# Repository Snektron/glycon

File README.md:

nin# Glycon

## Dependencies

* meson
* ninja or samurai
* avr-binutils
* avr-gcc
* avr-libc

## Compiling

### Coprocessor

```
$ mkdir -p build/glyco
$ cd build/glyco
$ meson ../.. --cross-file ../../cross/avr-atmega2560-cross.ini
$ ninja
```

To use the provided `flash` target to flash the coprocessor, set the coprocessor port the arduino is connected with by passing `-Dport=/dev/<port>` to meson (usually /dev/ttyUSB0) and add yourself to to appropriate groups (typically `dialout` or `uucp`).

### Debugger

```
$ mkdir -p build/glydb
$ cd build/glydb
$ meson ../..
$ ninja
```

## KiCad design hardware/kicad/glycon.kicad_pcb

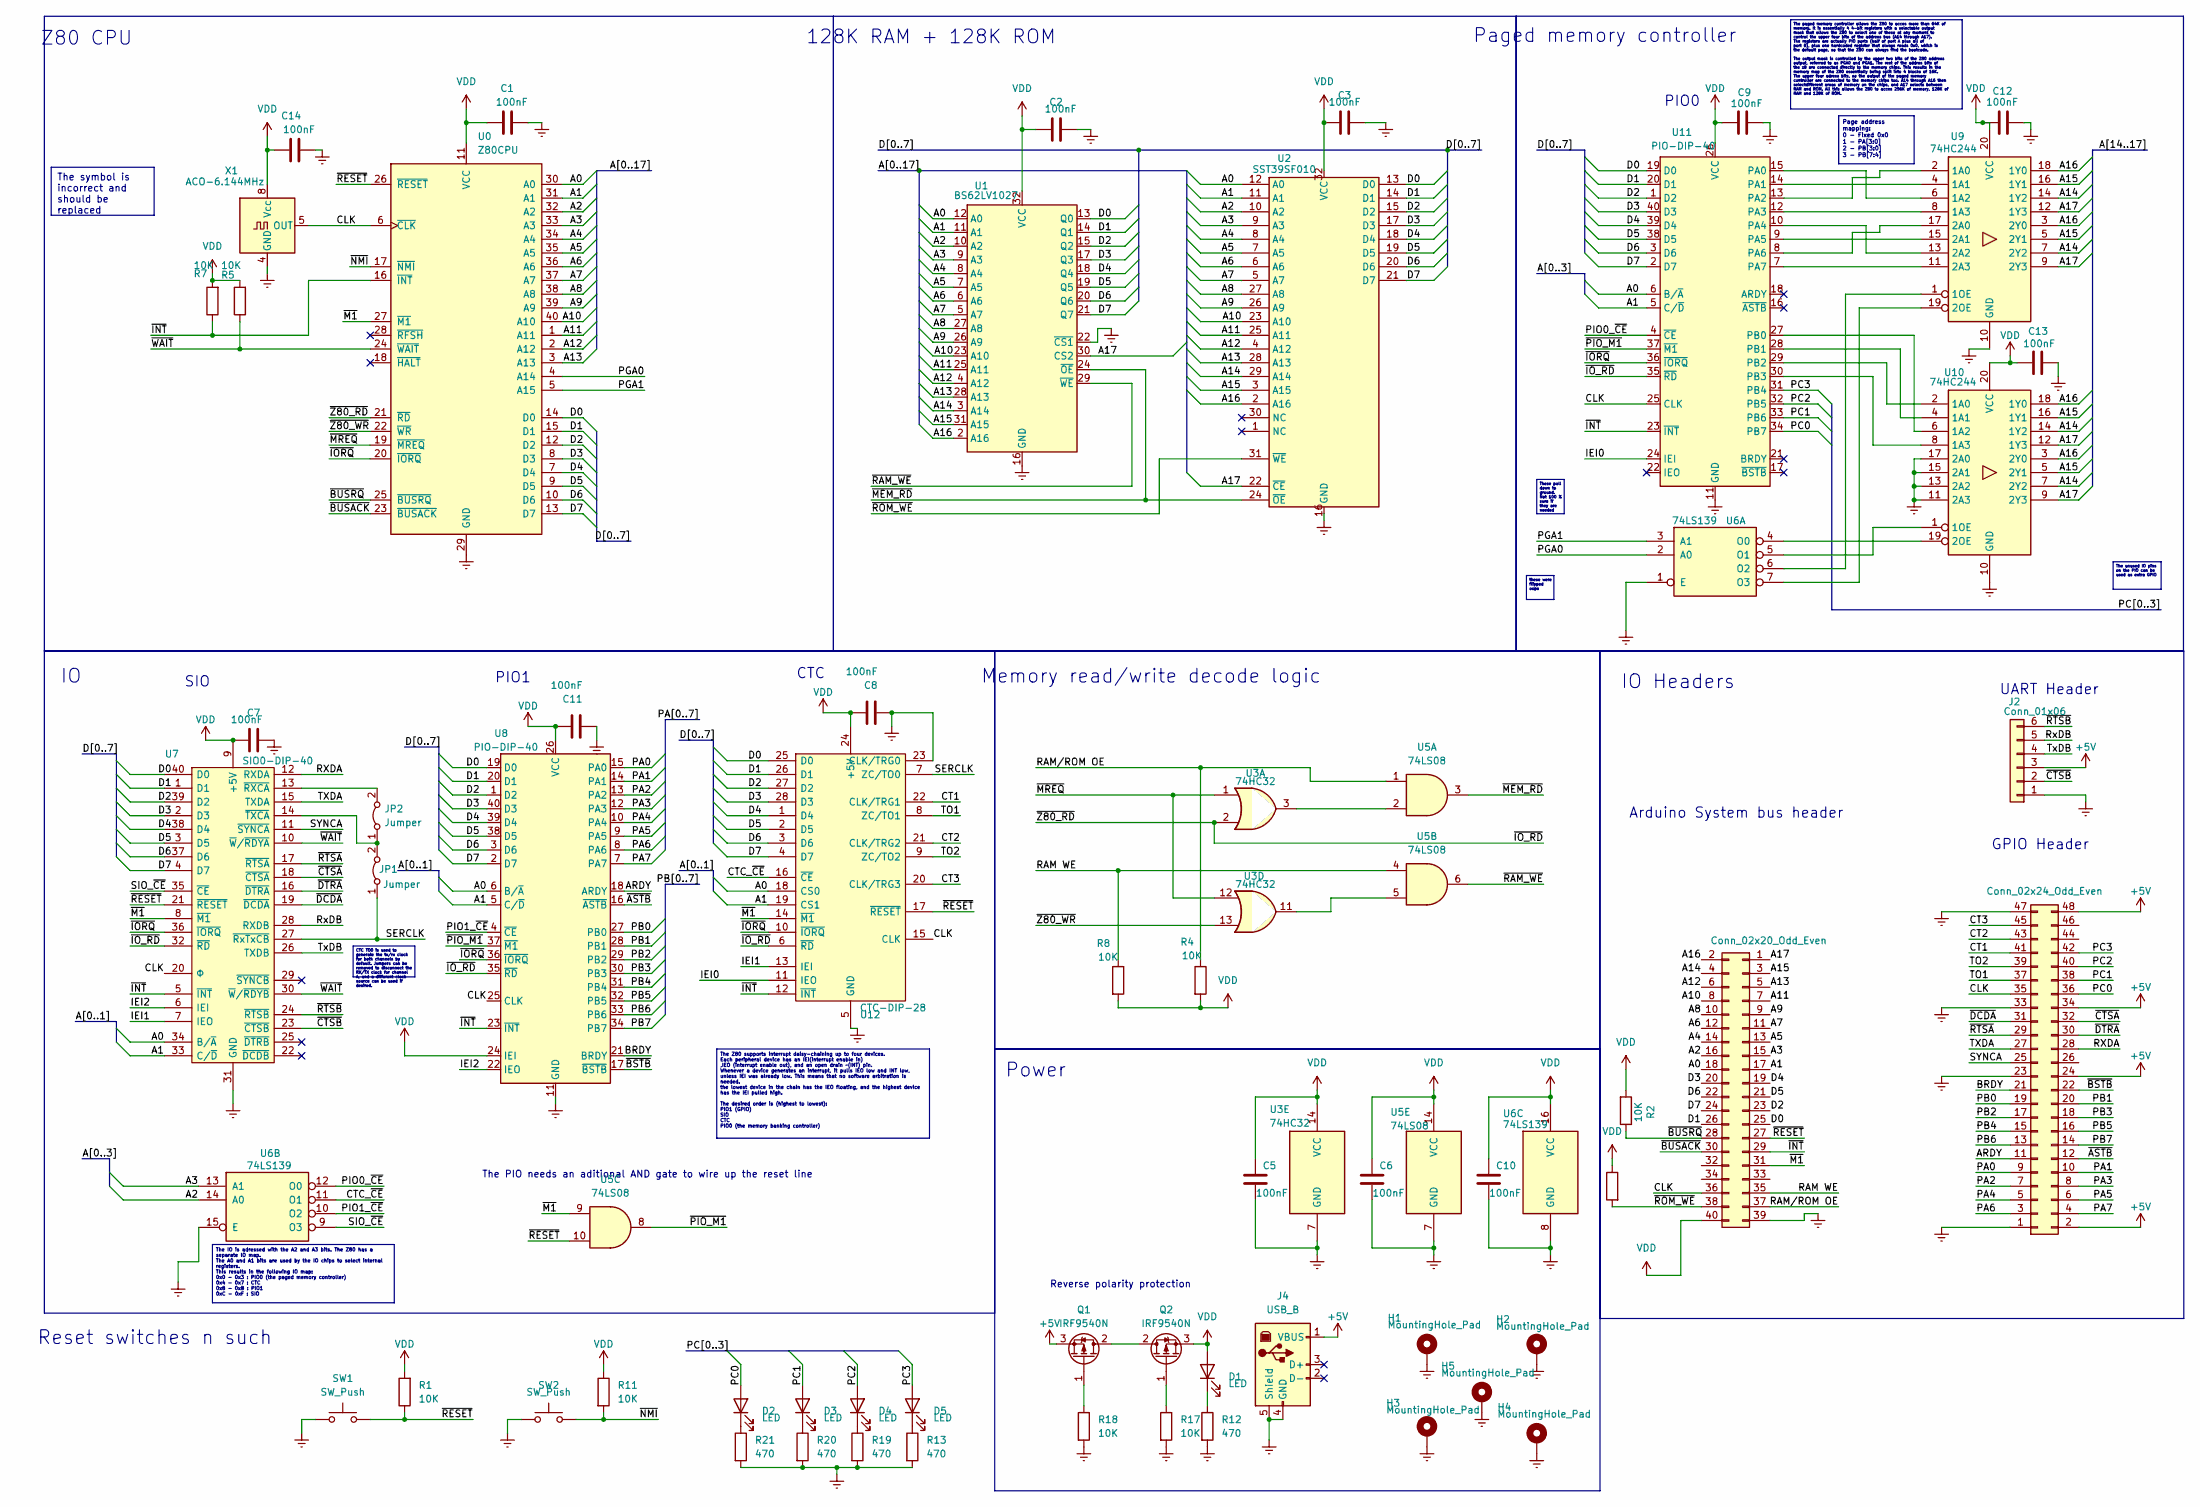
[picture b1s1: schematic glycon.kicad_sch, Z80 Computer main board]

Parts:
C1, C2, C3, C5, C6, C7, C8, C9, C10, C11, C12, C13, C14: 100nF; C_Disc_D4.7mm_W2.5mm_P5.00mm
D1, D2, D3, D4, D5: LED; LED_D5.0mm
H1, H2, H3, H4, H5: MountingHole_Pad; MountingHole_3.2mm_M3_Pad
J1: Conn_02x20_Odd_Even; PinSocket_2x20_P2.54mm_Vertical
J2: Conn_01x06; PinHeader_1x06_P2.54mm_Vertical
J3: Conn_02x24_Odd_Even; PinSocket_2x24_P2.54mm_Vertical
J4: USB_B; USB_B_TE_5787834_Vertical
JP1, JP2: Jumper; PinHeader_2x01_P2.54mm_Vertical
Q1, Q2: IRF9540N; TO-220-3_Vertical
R1, R2, R3, R4, R5, R7, R8, R11, R17, R18: 10K; R_Axial_DIN0207_L6.3mm_D2.5mm_P10.16mm_Horizontal
R12, R13, R19, R20, R21: 470; R_Axial_DIN0207_L6.3mm_D2.5mm_P10.16mm_Horizontal
SW1, SW2: SW_Push; SW_PUSH_6mm
U0: Z80CPU; DIP-40_W15.24mm_Socket
U1: BS62LV1027; DIP-32_W15.24mm_Socket
U2: SST39SF010; DIP-32_W15.24mm_Socket
U3: 74HC32; DIP-14_W7.62mm_Socket
U5: 74LS08; DIP-14_W7.62mm_Socket
U6: 74LS139; DIP-16_W7.62mm_Socket
U7: SIO0-DIP-40; DIP-40_W15.24mm_Socket; Manufacturer_Part_Number Z84C4206PEG; Mouser Part Number 692-Z84C4206PEG
U8, U11: PIO-DIP-40; DIP-40_W15.24mm_Socket
U9, U10: 74HC244; DIP-20_W7.62mm_Socket
U12: CTC-DIP-28; DIP-28_W15.24mm_Socket; Manufacturer_Part_Number Z84C3010PEG; Mouser Part Number 692-Z84C3010PEG
X1: ACO-6.144MHz; Oscillator_DIP-8

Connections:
+5V: J2.3, J3.2, J3.24, J3.34, J3.48, J4.1 (VBUS), Q1.3 (S)
/A0: J1.18, U0.30 (A0), U1.12 (A0), U2.12 (A0), U7.34 (B/~A), U8.6 (B/~A), U11.6 (B/~A), U12.18 (CS0)
/A1: J1.17, U0.31 (A1), U1.11 (A1), U2.11 (A1), U7.33 (C/~D), U8.5 (C/~D), U11.5 (C/~D), U12.19 (CS1)
/A2: J1.16, U0.32 (A2), U1.10 (A2), U2.10 (A2), U6.14 (A0)
/A3: J1.15, U0.33 (A3), U1.9 (A3), U2.9 (A3), U6.13 (A1)
/A4: J1.14, U0.34 (A4), U1.8 (A4), U2.8 (A4)
/A5: J1.13, U0.35 (A5), U1.7 (A5), U2.7 (A5)
/A6: J1.12, U0.36 (A6), U1.6 (A6), U2.6 (A6)
/A7: J1.11, U0.37 (A7), U1.5 (A7), U2.5 (A7)
/A8: J1.10, U0.38 (A8), U1.27 (A8), U2.27 (A8)
/A9: J1.9, U0.39 (A9), U1.26 (A9), U2.26 (A9)
/A10: J1.8, U0.40 (A10), U1.23 (A10), U2.23 (A10)
/A11: J1.7, U0.1 (A11), U1.25 (A11), U2.25 (A11)
/A12: J1.6, U0.2 (A12), U1.4 (A12), U2.4 (A12)
/A13: J1.5, U0.3 (A13), U1.28 (A13), U2.28 (A13)
/A14: J1.4, U1.3 (A14), U2.29 (A14), U9.7 (2Y2), U9.14 (1Y2), U10.7 (2Y2), U10.14 (1Y2)
/A15: J1.3, U1.31 (A15), U2.3 (A15), U9.5 (2Y1), U9.16 (1Y1), U10.5 (2Y1), U10.16 (1Y1)
/A16: J1.2, U1.2 (A16), U2.2 (A16), U9.3 (2Y0), U9.18 (1Y0), U10.3 (2Y0), U10.18 (1Y0)
/A17: J1.1, U1.30 (CS2), U2.22 (~CE), U9.9 (2Y3), U9.12 (1Y3), U10.9 (2Y3), U10.12 (1Y3)
/ARDY: J3.11, U8.18 (ARDY)
/BRDY: J3.21, U8.21 (BRDY)
/CLK: J1.36, J3.35, U0.6 (~CLK), U7.20 (Φ), U8.25 (CLK), U11.25 (CLK), U12.15 (CLK), X1.5 (OUT)
/CT1: J3.41, U12.22 (CLK/TRG1)
/CT2: J3.43, U12.21 (CLK/TRG2)
/CT3: J3.45, U12.20 (CLK/TRG3)
/CTC_~CE: U6.11 (O1), U12.16 (~CE)
/D0: J1.25, U0.14 (D0), U1.13 (Q0), U2.13 (D0), U7.40 (D0), U8.19 (D0), U11.19 (D0), U12.25 (D0)
/D1: J1.26, U0.15 (D1), U1.14 (Q1), U2.14 (D1), U7.1 (D1), U8.20 (D1), U11.20 (D1), U12.26 (D1)
/D2: J1.23, U0.12 (D2), U1.15 (Q2), U2.15 (D2), U7.39 (D2), U8.1 (D2), U11.1 (D2), U12.27 (D2)
/D3: J1.20, U0.8 (D3), U1.17 (Q3), U2.17 (D3), U7.2 (D3), U8.40 (D3), U11.40 (D3), U12.28 (D3)
/D4: J1.19, U0.7 (D4), U1.18 (Q4), U2.18 (D4), U7.38 (D4), U8.39 (D4), U11.39 (D4), U12.1 (D4)
/D5: J1.21, U0.9 (D5), U1.19 (Q5), U2.19 (D5), U7.3 (D5), U8.38 (D5), U11.38 (D5), U12.2 (D5)
/D6: J1.22, U0.10 (D6), U1.20 (Q6), U2.20 (D6), U7.37 (D6), U8.3 (D6), U11.3 (D6), U12.3 (D6)
/D7: J1.24, U0.13 (D7), U1.21 (Q7), U2.21 (D7), U7.4 (D7), U8.2 (D7), U11.2 (D7), U12.4 (D7)
/IEI0: U11.24 (IEI), U12.11 (IEO)
/IEI1: U7.7 (IEO), U12.13 (IEI)
/IEI2: U7.6 (IEI), U8.22 (IEO)
/PA0: J3.9, U8.15 (PA0)
/PA1: J3.10, U8.14 (PA1)
/PA2: J3.7, U8.13 (PA2)
/PA3: J3.8, U8.12 (PA3)
/PA4: J3.5, U8.10 (PA4)
/PA5: J3.6, U8.9 (PA5)
/PA6: J3.3, U8.8 (PA6)
/PA7: J3.4, U8.7 (PA7)
/PB0: J3.19, U8.27 (PB0)
/PB1: J3.20, U8.28 (PB1)
/PB2: J3.17, U8.29 (PB2)
/PB3: J3.18, U8.30 (PB3)
/PB4: J3.15, U8.31 (PB4)
/PB5: J3.16, U8.32 (PB5)
/PB6: J3.13, U8.33 (PB6)
/PB7: J3.14, U8.34 (PB7)
/PC0: D2.2 (A), J3.36, U11.34 (PB7)
/PC1: D3.2 (A), J3.38, U11.33 (PB6)
/PC2: D4.2 (A), J3.40, U11.32 (PB5)
/PC3: D5.2 (A), J3.42, U11.31 (PB4)
/PGA0: U0.4 (A14), U6.2 (A0)
/PGA1: U0.5 (A15), U6.3 (A1)
/PIO0_~CE: U6.12 (O0), U11.4 (~CE)
/PIO1_~CE: U6.10 (O2), U8.4 (~CE)
/RAM WE: J1.35, R8.1, U5.4
/RAM/ROM OE: J1.37, R4.1, U5.1
/RXDA: J3.28, U7.12 (RXDA)
/RxDB: J2.5, U7.28 (RXDB)
/SERCLK: JP1.1 (A), U7.27 (~RxTxCB), U12.7 (ZC/TO0)
/SIO_~CE: U6.9 (O3), U7.35 (~CE)
/SYNCA: J3.25, U7.11 (~SYNCA)
/TO1: J3.37, U12.8 (ZC/TO1)
/TO2: J3.39, U12.9 (ZC/TO2)
/TXDA: J3.27, U7.15 (TXDA)
/TxDB: J2.4, U7.26 (TXDB)
/~ASTB: J3.12, U8.16 (~ASTB)
/~BSTB: J3.22, U8.17 (~BSTB)
/~BUSACK: J1.30, U0.23 (~BUSACK)
/~BUSRQ: J1.28, R2.1, U0.25 (~BUSRQ)
/~CTSA: J3.32, U7.18 (~CTSA)
/~CTSB: J2.2, U7.23 (~CTSB)
/~DCDA: J3.31, U7.19 (~DCDA)
/~DTRA: J3.30, U7.16 (~DTRA)
/~INT: J1.29, R7.1, U0.16 (~INT), U7.5 (~INT), U8.23 (~INT), U11.23 (~INT), U12.12 (~INT)
/~IORQ: U0.20 (~IORQ), U7.36 (~IORQ), U8.36 (~IORQ), U11.36 (~IORQ), U12.10 (~IORQ)
/~IO_RD: U0.21 (~RD), U3.2, U7.32 (~RD), U8.35 (~RD), U11.35 (~RD), U12.6 (~RD)
/~M1: J1.31, U0.27 (~M1), U5.9, U7.8 (~M1), U12.14 (~M1)
/~MEM_RD: U1.24 (~OE), U2.24 (~OE), U5.3
/~MREQ: U0.19 (~MREQ), U3.1, U3.12
/~NMI: R11.2, SW2.2, U0.17 (~NMI)
/~PIO_M1: U5.8, U8.37 (~M1), U11.37 (~M1)
/~RAM_WE: U1.29 (~WE), U5.6
/~RESET: J1.27, R1.1, SW1.2, U0.26 (~RESET), U5.10, U7.21 (~RESET), U12.17 (~RESET)
/~ROM_WE: J1.38, R3.2, U2.31 (~WE)
/~RTSA: J3.29, U7.17 (~RTSA)
/~RTSB: J2.6, U7.24 (~RTSB)
/~WAIT: R5.1, U0.24 (~WAIT), U7.10 (~W/~RDYA), U7.30 (~W/~RDYB)
/~Z80_WR: U0.22 (~WR), U3.13
Earth: C1.2, C2.2, C3.1, C5.2, C6.2, C7.2, C8.2, C9.1, C10.2, C11.2, C12.2, C13.2, C14.2, H1.1, H2.1, H3.1, H4.1, H5.1, J1.39, J2.1, J3.1, J3.23, J3.33, J3.47, J4.4 (GND), J4.5 (Shield), R12.2, R13.2, R17.2, R18.2, R19.2, R20.2, R21.2, SW1.1, SW2.1, U0.29 (GND), U1.16 (GND), U1.22 (~CS1), U2.16 (GND), U3.7 (GND), U5.7 (GND), U6.1 (E), U6.8 (GND), U6.15 (E), U7.31 (GND), U8.11 (GND), U9.10 (GND), U10.10 (GND), U10.11 (2A3), U10.13 (2A2), U10.15 (2A1), U10.17 (2A0), U11.11 (GND), U12.5 (GND), U12.23 (CLK/TRG0), X1.4 (GND)
unnamed: D1.1 (K), R12.1
unnamed: D2.1 (K), R21.1
unnamed: D3.1 (K), R20.1
unnamed: D4.1 (K), R19.1
unnamed: D5.1 (K), R13.1
unnamed: JP1.2 (B), JP2.1 (A), U7.14 (~TXCA)
unnamed: JP2.2 (B), U7.13 (~RXCA)
unnamed: Q1.2 (D), Q2.2 (D)
unnamed: Q1.1 (G), R18.1
unnamed: Q2.1 (G), R17.1
unnamed: U3.3, U5.2
unnamed: U3.11, U5.5
unnamed: U6.6 (O2), U9.1 (1OE)
unnamed: U6.7 (O3), U9.19 (2OE)
unnamed: U10.2 (1A0), U11.29 (PB2)
unnamed: U10.4 (1A1), U11.28 (PB1)
unnamed: U10.6 (1A2), U11.27 (PB0)
unnamed: U10.8 (1A3), U11.30 (PB3)
unnamed: U6.5 (O1), U10.1 (1OE)
unnamed: U6.4 (O0), U10.19 (2OE)
unnamed: U9.6 (1A2), U11.15 (PA0)
unnamed: U9.4 (1A1), U11.14 (PA1)
unnamed: U9.2 (1A0), U11.13 (PA2)
unnamed: U9.8 (1A3), U11.12 (PA3)
unnamed: U9.13 (2A2), U11.10 (PA4)
unnamed: U9.15 (2A1), U11.9 (PA5)
unnamed: U9.17 (2A0), U11.8 (PA6)
unnamed: U9.11 (2A3), U11.7 (PA7)
VDD: C1.1, C2.1, C3.2, C5.1, C6.1, C7.1, C8.1, C9.2, C10.1, C11.1, C12.1, C13.1, C14.1, D1.2 (A), J1.40, Q2.3 (S), R1.2, R2.2, R3.1, R4.2, R5.2, R7.2, R8.2, R11.1, U0.11 (VCC), U1.32 (VCC), U2.32 (VCC), U3.14 (VCC), U5.14 (VCC), U6.16 (VCC), U7.9 (+5V), U8.24 (IEI), U8.26 (VCC), U9.20 (VCC), U10.20 (VCC), U11.26 (VCC), U12.24 (+5V), X1.8 (Vcc)

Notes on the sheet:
CTC TO0 is used to generate the tx/rx clock for both channels by default. Jumpers can be removed to disconnect the RX/TX clock for channel A, and a different clock source can be used if desired.
The unused IO pins on the PIO can be used as extra GPIO
The IO is adressed with the A2 and A3 bits. The Z80 has a separate IO map. The A0 and A1 bits are used by the IO chips to select internal registers. This results in the following IO map: 0x0 - 0x3 : PIO0 (the paged memory controller) 0x4 - 0x7 : CTC 0x8 - 0xB : PIO1 0xC - 0xF : SIO
these were flipped oops
These pull down to ground. Not 100 % sure if they are needed
The Z80 supports interrupt daisy-chaining up to four devices. Each peripheral device has an IEI(interrupt enable in) ,IEO (interrupt enable out), and an open drain ~(INT) pin. Whenever a device generates an interrupt, it pulls IEO low and INT low, unless IEI was already low. This means that no soft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
The paged memory controller allows the Z80 to acces more than 64K of memory. It is essentially 4 4-bit registers with a selectable output mask that allows the Z80 to select one of these at any moment to control the upper four bits of the address bus (A14 through A17). The registers are actually PIO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
Page address mapping: 0 - Fixed 0x0 1 - PA[3:0] 2 - PB[3:0] 3 - PB[7:4]
The symbol is incorrect and should be replaced
Reset switches n such
UART Header
CTC
Power
PIO0
Z80 CPU
SIO
IO Headers
128K RAM + 128K ROM
The PIO needs an aditional AND gate to wire up the reset line
Paged memory controller
Reverse polarity protection
GPIO Header
Memory read/write decode logic
Arduino System bus header
PIO1

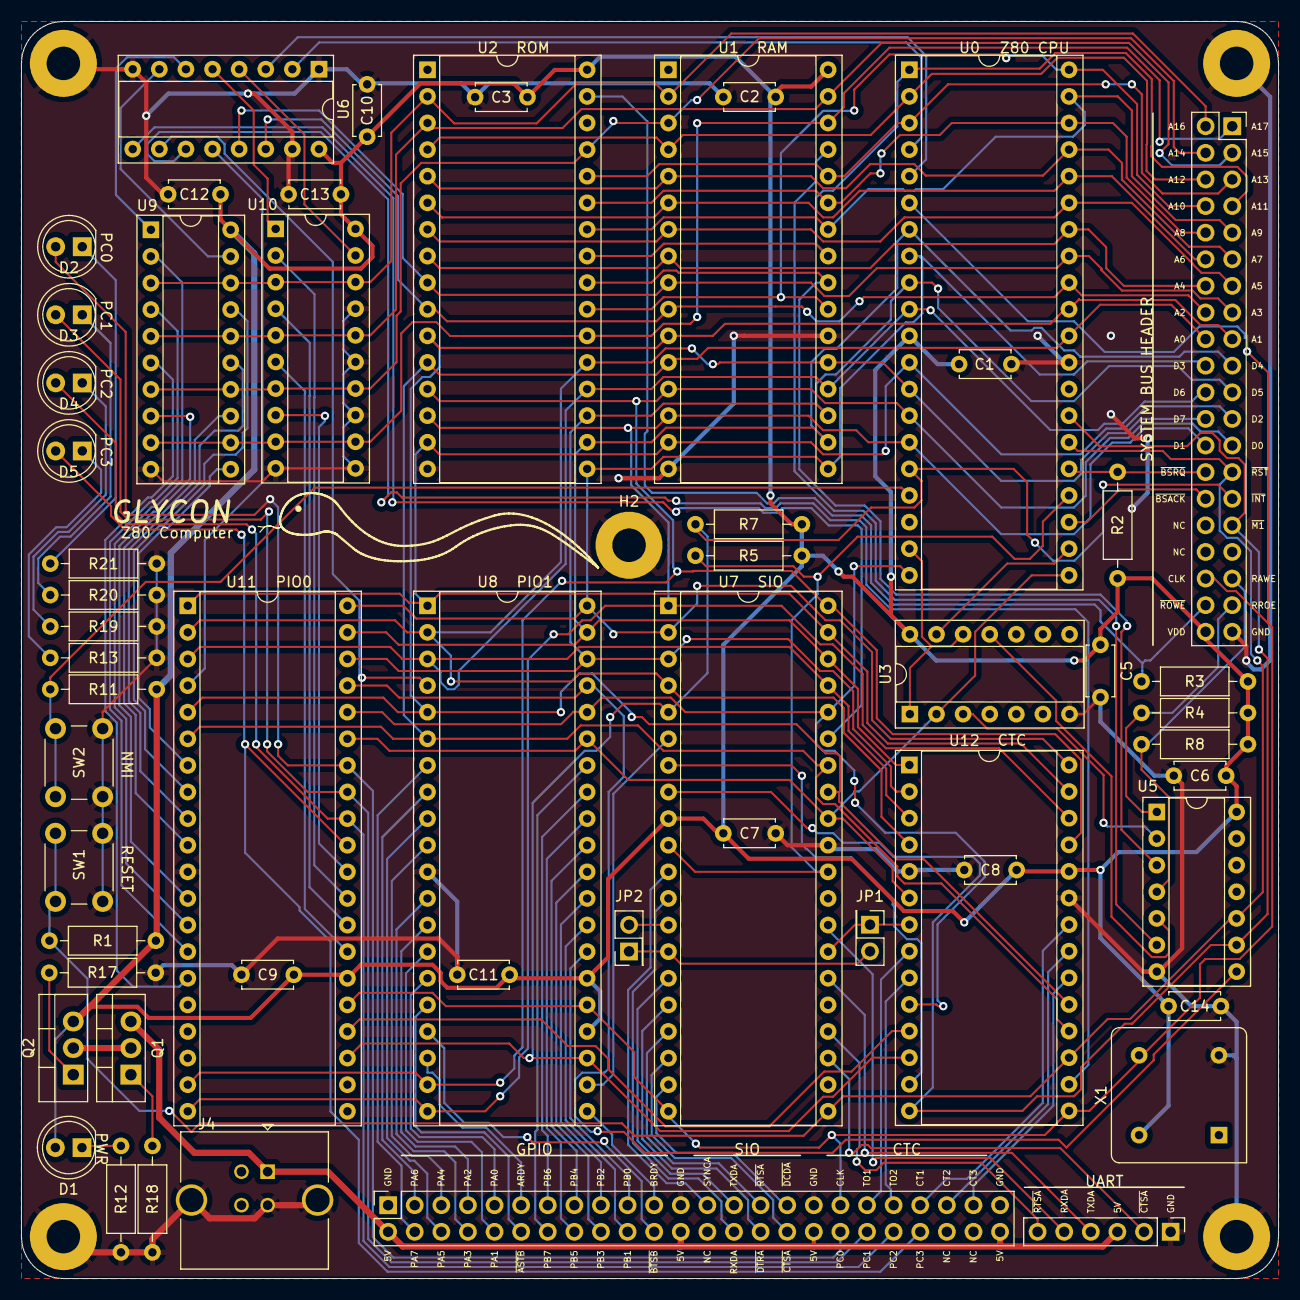
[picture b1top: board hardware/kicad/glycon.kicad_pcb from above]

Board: 2 copper layers, 120.0 x 120.0 mm, 61 parts (0 on the bottom side), 125 nets.

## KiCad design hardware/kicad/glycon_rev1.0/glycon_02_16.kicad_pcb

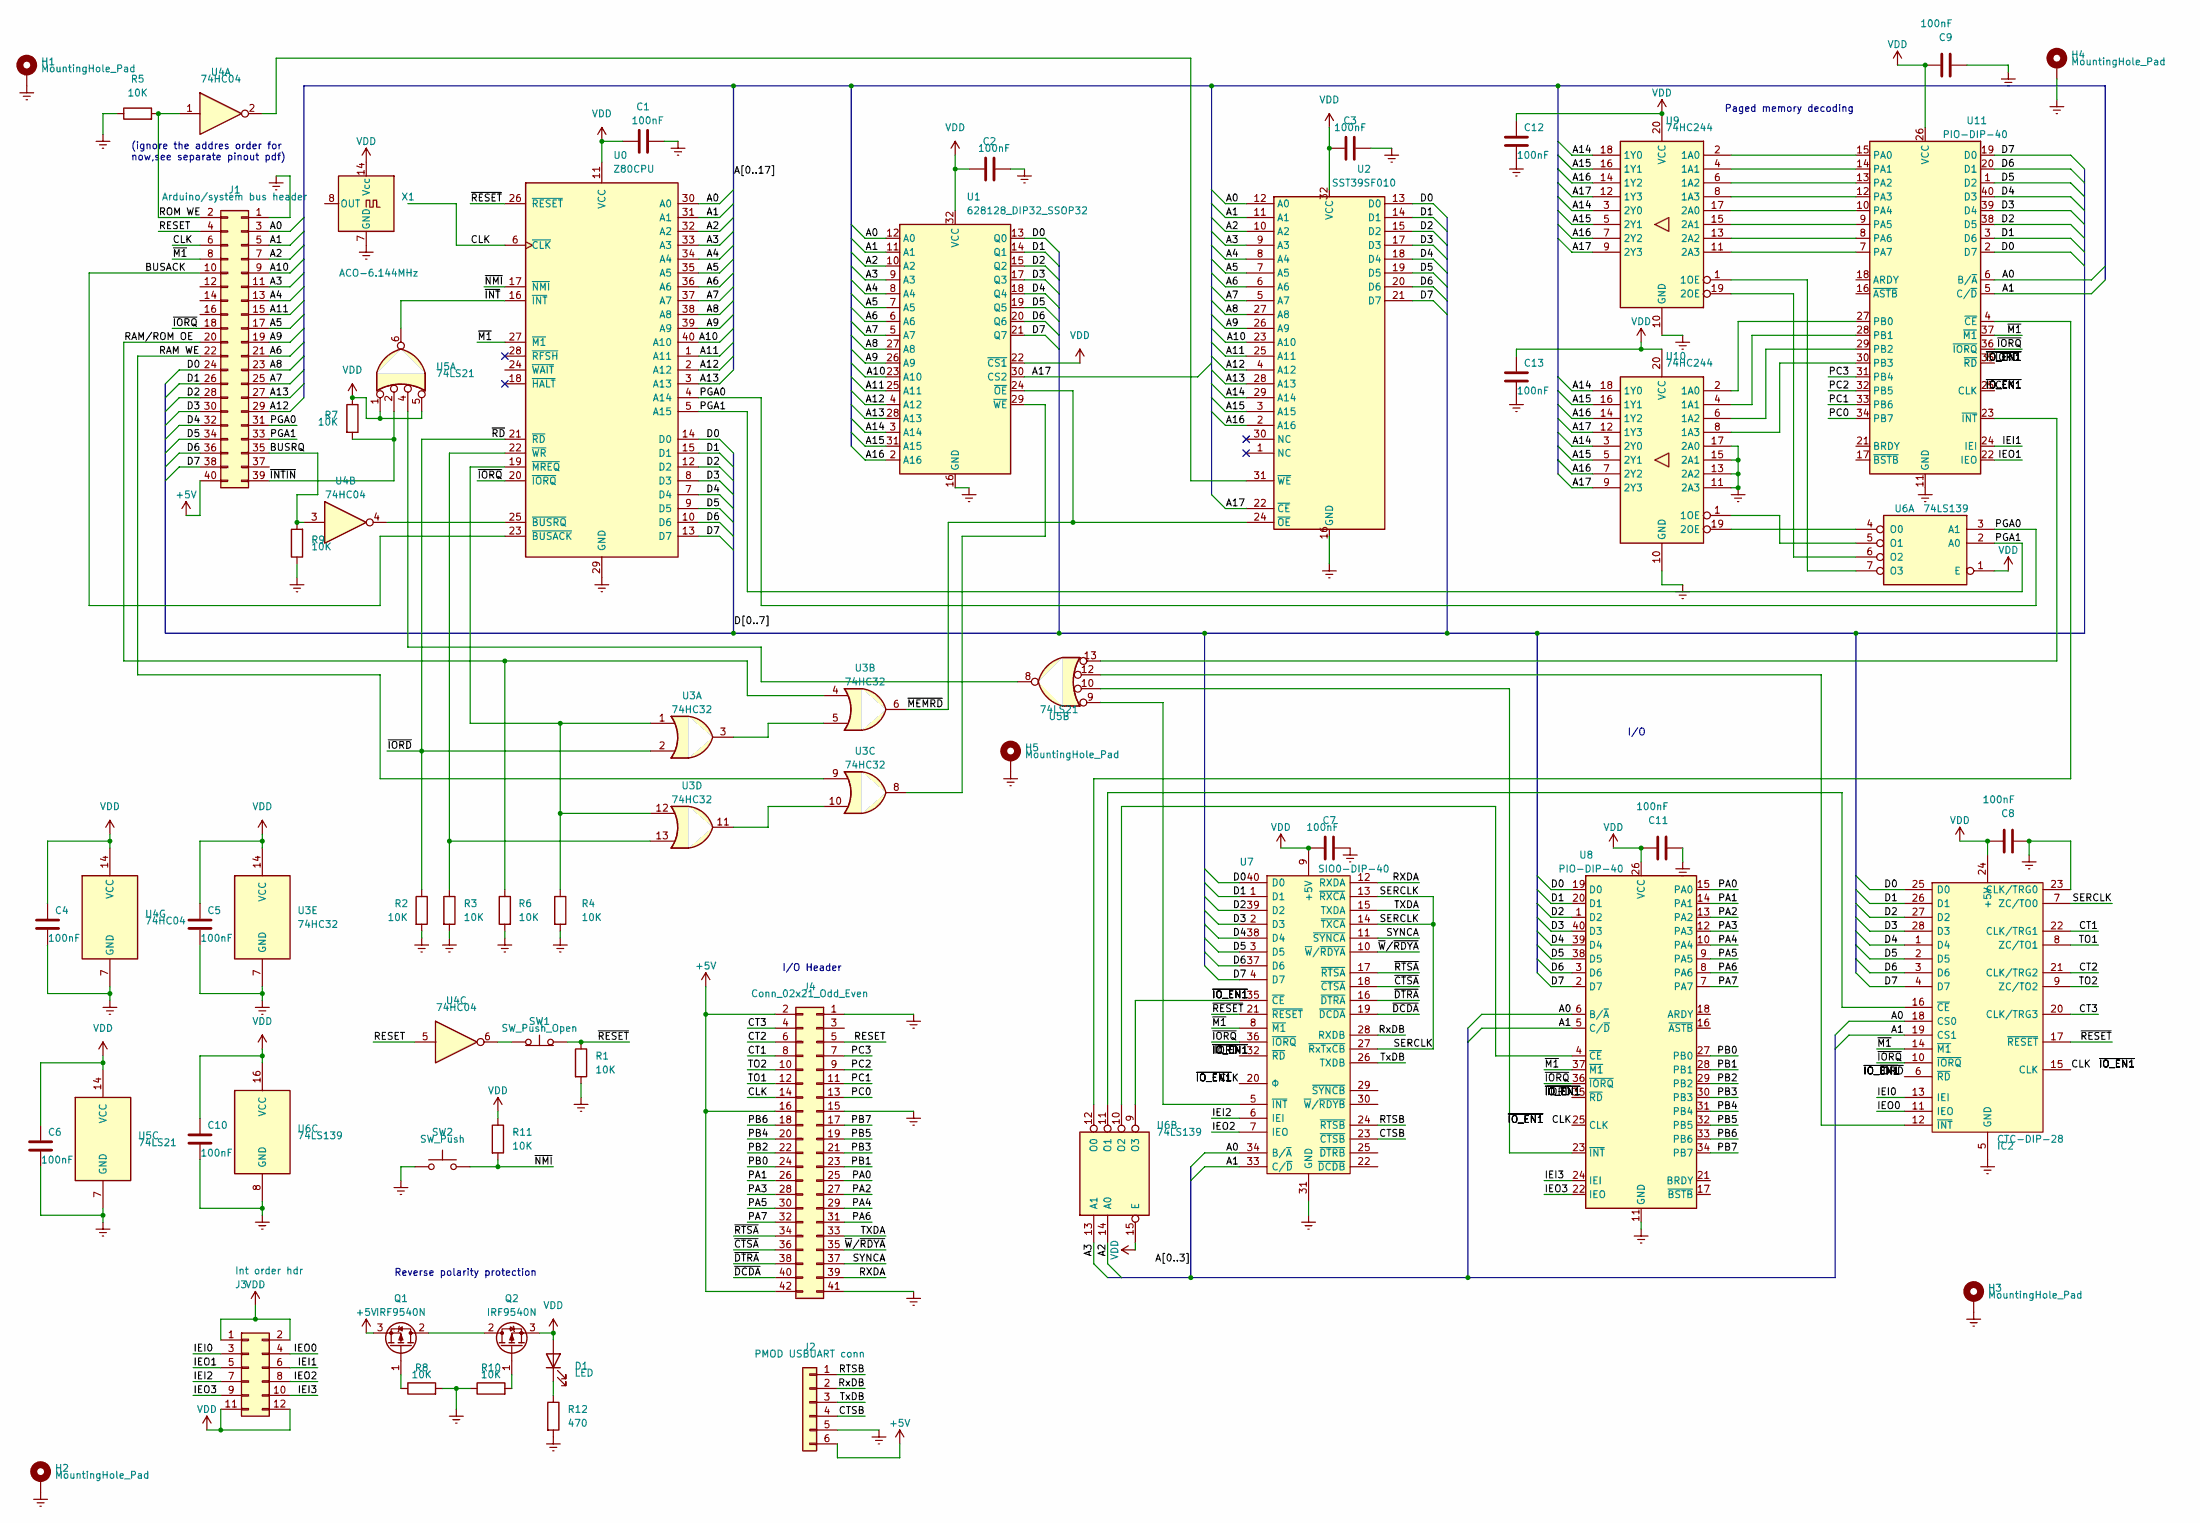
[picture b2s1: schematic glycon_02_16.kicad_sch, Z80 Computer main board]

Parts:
C1, C2, C3, C4, C5, C6, C7, C8, C9, C10, C11, C12, C13: 100nF; C_Disc_D4.7mm_W2.5mm_P5.00mm
D1: LED; LED_D5.0mm
H1, H2, H3, H4, H5: MountingHole_Pad; MountingHole_3.2mm_M3_Pad
IC2: CTC-DIP-28; DIP-28_W15.24mm_Socket; Manufacturer_Part_Number Z84C3010PEG; Mouser Part Number 692-Z84C3010PEG
J1: Arduino/system bus header; PinSocket_2x20_P2.54mm_Vertical
J2: PMOD USBUART conn; PinHeader_1x06_P2.54mm_Vertical
J3: Int order hdr; PinHeader_2x06_P2.54mm_Vertical
J4: Conn_02x21_Odd_Even; PinSocket_2x21_P2.54mm_Vertical
Q1, Q2: IRF9540N; TO-220-3_Vertical
R1, R2, R3, R4, R5, R6, R7, R8, R9, R10, R11: 10K; R_Axial_DIN0204_L3.6mm_D1.6mm_P5.08mm_Horizontal
R12: 470; R_Axial_DIN0204_L3.6mm_D1.6mm_P5.08mm_Horizontal
SW1: SW_Push_Open; SW_PUSH_6mm
SW2: SW_Push; SW_PUSH_6mm
U0: Z80CPU; DIP-40_W15.24mm_Socket
U1: 628128_DIP32_SSOP32; DIP-32_W15.24mm_Socket
U2: SST39SF010; DIP-32_W15.24mm_Socket
U3: 74HC32; DIP-14_W7.62mm_Socket
U4: 74HC04; DIP-14_W7.62mm_Socket
U5: 74LS21; DIP-14_W7.62mm_Socket
U6: 74LS139; DIP-16_W7.62mm_Socket
U7: SIO0-DIP-40; DIP-40_W15.24mm_Socket; Manufacturer_Part_Number Z84C4206PEG; Mouser Part Number 692-Z84C4206PEG
U8, U11: PIO-DIP-40; DIP-40_W15.24mm_Socket
U9, U10: 74HC244; DIP-20_W7.62mm_Socket
X1: ACO-6.144MHz; Oscillator_DIP-14

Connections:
+5V: J1.40, J2.6, J4.2, J4.16, J4.42, Q1.3 (S)
/A0: IC2.18 (CS0), J1.3, U0.30 (A0), U1.12 (A0), U2.12 (A0), U7.34 (B/~A), U8.6 (B/~A), U11.6 (B/~A)
/A1: IC2.19 (CS1), J1.5, U0.31 (A1), U1.11 (A1), U2.11 (A1), U7.33 (C/~D), U8.5 (C/~D), U11.5 (C/~D)
/A2: J1.7, U0.32 (A2), U1.10 (A2), U2.10 (A2), U6.14 (A0)
/A3: J1.11, U0.33 (A3), U1.9 (A3), U2.9 (A3), U6.13 (A1)
/A4: J1.13, U0.34 (A4), U1.8 (A4), U2.8 (A4)
/A5: J1.17, U0.35 (A5), U1.7 (A5), U2.7 (A5)
/A6: J1.21, U0.36 (A6), U1.6 (A6), U2.6 (A6)
/A7: J1.25, U0.37 (A7), U1.5 (A7), U2.5 (A7)
/A8: J1.23, U0.38 (A8), U1.27 (A8), U2.27 (A8)
/A9: J1.19, U0.39 (A9), U1.26 (A9), U2.26 (A9)
/A10: J1.9, U0.40 (A10), U1.23 (A10), U2.23 (A10)
/A11: J1.15, U0.1 (A11), U1.25 (A11), U2.25 (A11)
/A12: J1.29, U0.2 (A12), U1.4 (A12), U2.4 (A12)
/A13: J1.27, U0.3 (A13), U1.28 (A13), U2.28 (A13)
/A14: U1.3 (A14), U2.29 (A14), U9.3 (2Y0), U9.18 (1Y0), U10.3 (2Y0), U10.18 (1Y0)
/A15: U1.31 (A15), U2.3 (A15), U9.5 (2Y1), U9.16 (1Y1), U10.5 (2Y1), U10.16 (1Y1)
/A16: U1.2 (A16), U2.2 (A16), U9.7 (2Y2), U9.14 (1Y2), U10.7 (2Y2), U10.14 (1Y2)
/A17: U1.30 (CS2), U2.22 (~CE), U9.9 (2Y3), U9.12 (1Y3), U10.9 (2Y3), U10.12 (1Y3)
/BUSACK: J1.10, U0.23 (~BUSACK)
/BUSRQ: J1.35, R9.2, U4.3
/CLK: IC2.15 (CLK), J1.6, J4.14, U0.6 (~CLK), U7.20 (Φ), U8.25 (CLK), U11.25 (CLK), X1.1 (NC), X1.8 (OUT)
/CT1: IC2.22 (CLK/TRG1), J4.8
/CT2: IC2.21 (CLK/TRG2), J4.6
/CT3: IC2.20 (CLK/TRG3), J4.4
/CTSB: J2.4, U7.23 (~CTSB)
/D0: IC2.25 (D0), J1.24, U0.14 (D0), U1.13 (Q0), U2.13 (D0), U7.40 (D0), U8.19 (D0), U11.2 (D7)
/D1: IC2.26 (D1), J1.26, U0.15 (D1), U1.14 (Q1), U2.14 (D1), U7.1 (D1), U8.20 (D1), U11.3 (D6)
/D2: IC2.27 (D2), J1.28, U0.12 (D2), U1.15 (Q2), U2.15 (D2), U7.39 (D2), U8.1 (D2), U11.38 (D5)
/D3: IC2.28 (D3), J1.30, U0.8 (D3), U1.17 (Q3), U2.17 (D3), U7.2 (D3), U8.40 (D3), U11.39 (D4)
/D4: IC2.1 (D4), J1.32, U0.7 (D4), U1.18 (Q4), U2.18 (D4), U7.38 (D4), U8.39 (D4), U11.40 (D3)
/D5: IC2.2 (D5), J1.34, U0.9 (D5), U1.19 (Q5), U2.19 (D5), U7.3 (D5), U8.38 (D5), U11.1 (D2)
/D6: IC2.3 (D6), J1.36, U0.10 (D6), U1.20 (Q6), U2.20 (D6), U7.37 (D6), U8.3 (D6), U11.20 (D1)
/D7: IC2.4 (D7), J1.38, U0.13 (D7), U1.21 (Q7), U2.21 (D7), U7.4 (D7), U8.2 (D7), U11.19 (D0)
/IEI0: IC2.13 (IEI), J3.3
/IEI1: J3.6, U11.24 (IEI)
/IEI2: J3.7, U7.6 (IEI)
/IEI3: J3.10, U8.24 (IEI)
/IEO0: IC2.11 (IEO), J3.4
/IEO1: J3.5, U11.22 (IEO)
/IEO2: J3.8, U7.7 (IEO)
/IEO3: J3.9, U8.22 (IEO)
/PA0: J4.25, U8.15 (PA0)
/PA1: J4.26, U8.14 (PA1)
/PA2: J4.27, U8.13 (PA2)
/PA3: J4.28, U8.12 (PA3)
/PA4: J4.29, U8.10 (PA4)
/PA5: J4.30, U8.9 (PA5)
/PA6: J4.31, U8.8 (PA6)
/PA7: J4.32, U8.7 (PA7)
/PB0: J4.24, U8.27 (PB0)
/PB1: J4.23, U8.28 (PB1)
/PB2: J4.22, U8.29 (PB2)
/PB3: J4.21, U8.30 (PB3)
/PB4: J4.20, U8.31 (PB4)
/PB5: J4.19, U8.32 (PB5)
/PB6: J4.18, U8.33 (PB6)
/PB7: J4.17, U8.34 (PB7)
/PC0: J4.13, U11.34 (PB7)
/PC1: J4.11, U11.33 (PB6)
/PC2: J4.9, U11.32 (PB5)
/PC3: J4.7, U11.31 (PB4)
/PGA0: J1.31, U0.4 (A14), U6.3 (A1)
/PGA1: J1.33, U0.5 (A15), U6.2 (A0)
/RAM WE: J1.22, U3.9
/RAM/ROM OE: J1.20, R6.1, U3.4
/RESET: J1.4, J4.5, U4.5
/ROM WE: J1.2, R5.2, U4.1
/RTSB: J2.1, U7.24 (~RTSB)
/RXDA: J4.39, U7.12 (RXDA)
/RxDB: J2.2, U7.28 (RXDB)
/SERCLK: IC2.7 (ZC/TO0), U7.13 (~RXCA), U7.14 (~TXCA), U7.27 (~RxTxCB)
/SYNCA: J4.37, U7.11 (~SYNCA)
/TO1: IC2.8 (ZC/TO1), J4.12
/TO2: IC2.9 (ZC/TO2), J4.10
/TXDA: J4.33, U7.15 (TXDA)
/TxDB: J2.3, U7.26 (TXDB)
/~CTSA: J4.36, U7.18 (~CTSA)
/~DCDA: J4.40, U7.19 (~DCDA)
/~DTRA: J4.38, U7.16 (~DTRA)
/~INTIN: J1.39, R7.2, U5.2
/~INT: U0.16 (~INT), U5.6
/~IORQ: IC2.10 (~IORQ), J1.18, U0.20 (~IORQ), U7.36 (~IORQ), U8.36 (~IORQ), U11.36 (~IORQ)
/~IO_EN1: U6.9 (O3), U7.35 (~CE)
/~M1: IC2.14 (~M1), J1.8, U0.27 (~M1), U7.8 (~M1), U8.37 (~M1), U11.37 (~M1)
/~MEMRD: U1.24 (~OE), U2.24 (~OE), U3.6
/~NMI: R11.2, SW2.2, U0.17 (~NMI)
/~RESET: IC2.17 (~RESET), R1.1, SW1.2 (B), U0.26 (~RESET), U7.21 (~RESET)
/~RTSA: J4.34, U7.17 (~RTSA)
/~W/~RDYA: J4.35, U7.10 (~W/~RDYA)
Earth: C1.2, C2.2, C3.1, C4.2, C5.2, C6.2, C7.2, C8.2, C9.2, C10.2, C11.2, C12.2, C13.2, H1.1, H2.1, H3.1, H4.1, H5.1, IC2.5 (GND), IC2.23 (CLK/TRG0), J1.1, J2.5, J4.1, J4.15, J4.41, R1.2, R2.2, R3.2, R4.2, R5.1, R6.2, R8.2, R9.1, R10.1, R12.2, SW2.1, U0.29 (GND), U1.16 (GND), U2.16 (GND), U3.7 (GND), U4.7 (GND), U5.7 (GND), U6.8 (GND), U7.31 (GND), U8.11 (GND), U9.10 (GND), U10.10 (GND), U10.11 (2A3), U10.13 (2A2), U10.15 (2A1), U10.17 (2A0), U11.11 (GND), X1.7 (GND)
unnamed: D1.1 (K), R12.1
unnamed: IC2.16 (~CE), U6.11 (O1)
unnamed: IC2.12 (~INT), U5.12
unnamed: Q1.2 (D), Q2.2 (D)
unnamed: Q1.1 (G), R8.1
unnamed: Q2.1 (G), R10.2
unnamed: SW1.1 (A), U4.6
unnamed: U0.25 (~BUSRQ), U4.4
unnamed: R4.1, U0.19 (~MREQ), U3.1, U3.12
unnamed: R3.1, U0.22 (~WR), U3.13
unnamed: U1.29 (~WE), U3.8
unnamed: U2.31 (~WE), U4.2
unnamed: U3.3, U3.5
unnamed: U3.10, U3.11
unnamed: U5.4, U5.8
unnamed: U6.6 (O2), U9.19 (2OE)
unnamed: U6.7 (O3), U9.1 (1OE)
unnamed: U6.10 (O2), U8.4 (~CE)
unnamed: U5.9, U7.5 (~INT)
unnamed: U5.10, U8.23 (~INT)
unnamed: U10.2 (1A0), U11.27 (PB0)
unnamed: U10.4 (1A1), U11.28 (PB1)
unnamed: U10.6 (1A2), U11.29 (PB2)
unnamed: U10.8 (1A3), U11.30 (PB3)
unnamed: U6.5 (O1), U10.1 (1OE)
unnamed: U6.4 (O0), U10.19 (2OE)
unnamed: U9.2 (1A0), U11.15 (PA0)
unnamed: U9.4 (1A1), U11.14 (PA1)
unnamed: U9.6 (1A2), U11.13 (PA2)
unnamed: U9.8 (1A3), U11.12 (PA3)
unnamed: U9.17 (2A0), U11.10 (PA4)
unnamed: U9.15 (2A1), U11.9 (PA5)
unnamed: U9.13 (2A2), U11.8 (PA6)
unnamed: U9.11 (2A3), U11.7 (PA7)
unnamed: U6.12 (O0), U11.4 (~CE)
unnamed: U5.13, U11.23 (~INT)
VDD: C1.1, C2.1, C3.2, C4.1, C5.1, C6.1, C7.1, C8.1, C9.1, C10.1, C11.1, C12.1, C13.1, D1.2 (A), IC2.24 (+5V), J3.1, J3.2, J3.11, J3.12, Q2.3 (S), R7.1, R11.1, U0.11 (VCC), U1.22 (~CS1), U1.32 (VCC), U2.32 (VCC), U3.14 (VCC), U4.14 (VCC), U5.1, U5.5, U5.14 (VCC), U6.1 (E), U6.15 (E), U6.16 (VCC), U7.9 (+5V), U8.26 (VCC), U9.20 (VCC), U10.20 (VCC), U11.26 (VCC), X1.14 (Vcc)

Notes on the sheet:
I/O
Paged memory decoding
Reverse polarity protection
I/O Header
(ignore the addres order for now,see separate pinout pdf)

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
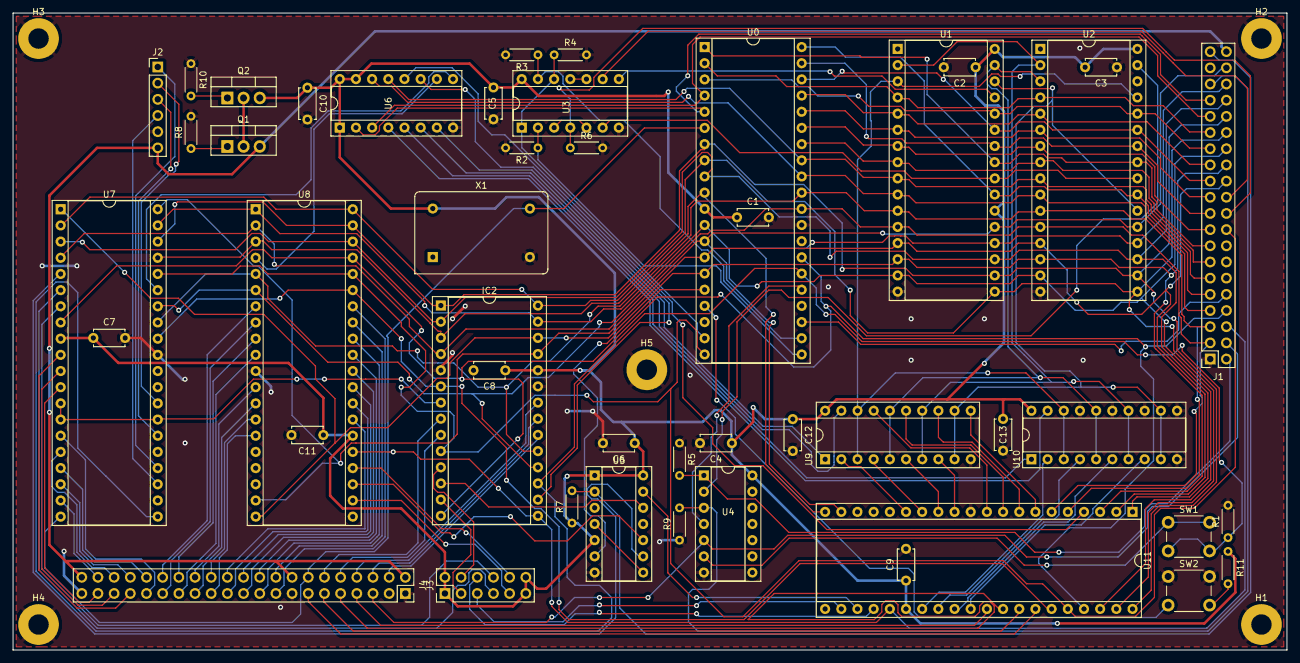
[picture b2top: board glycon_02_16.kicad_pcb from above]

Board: 2 copper layers, 200.0 x 100.0 mm, 51 parts (0 on the bottom side), 129 nets.
